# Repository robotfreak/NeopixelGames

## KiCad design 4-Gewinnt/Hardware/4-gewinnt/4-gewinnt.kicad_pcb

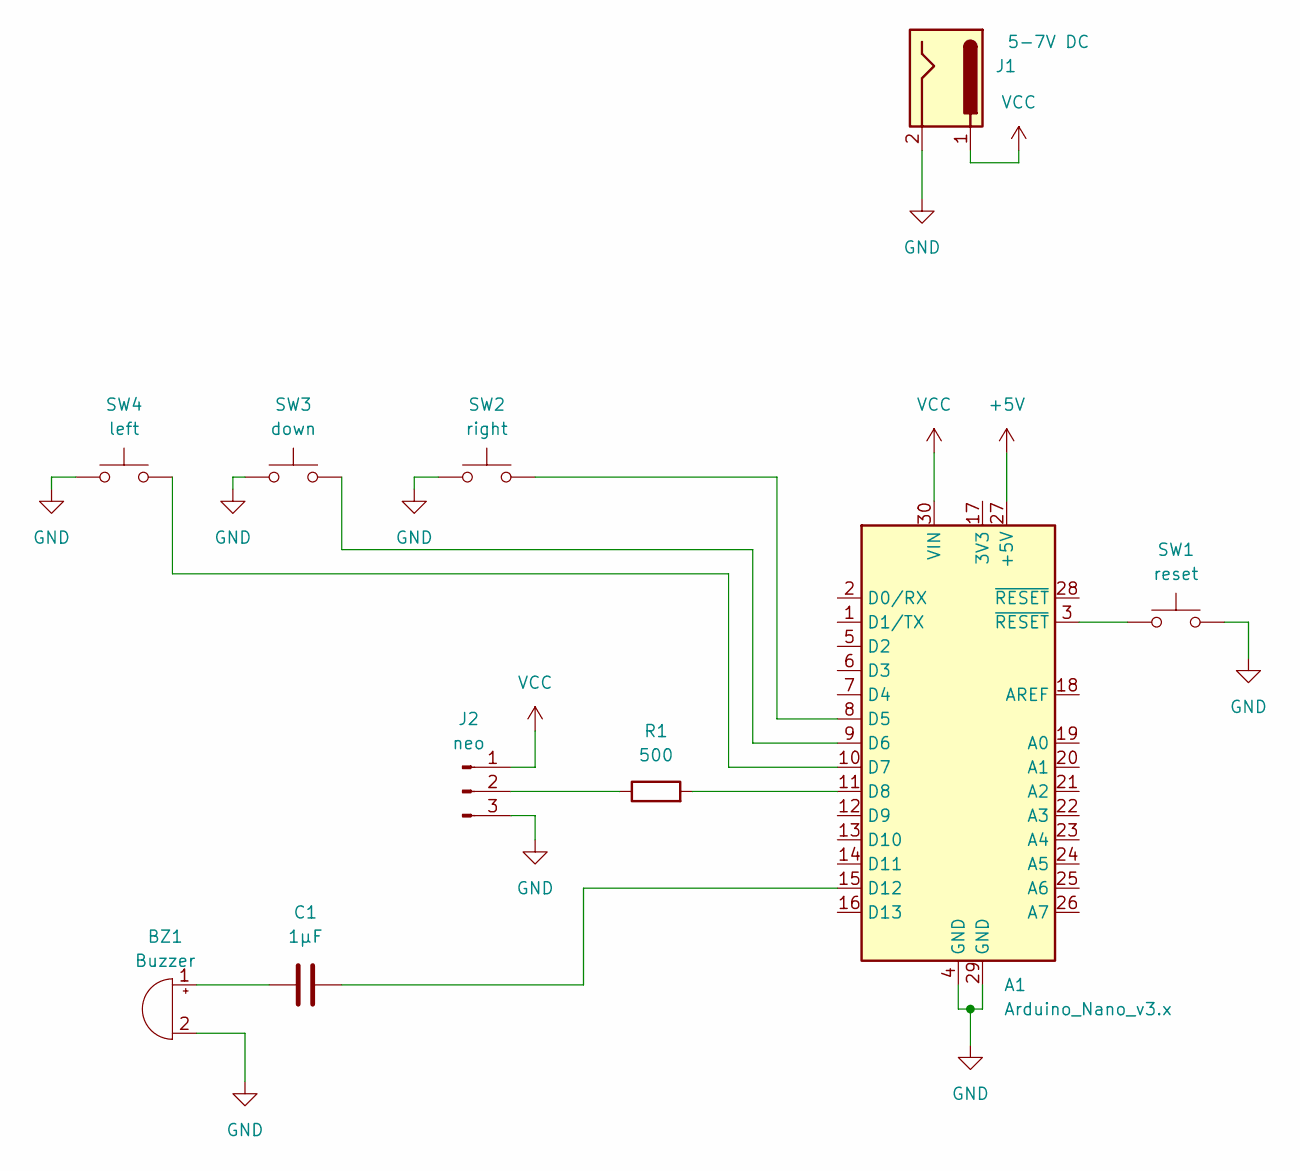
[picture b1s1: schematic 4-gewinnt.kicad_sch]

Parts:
A1: Arduino_Nano_v3.x; Arduino_Nano
BZ1: Buzzer; Buzzer_12x9.5RM7.6
C1: 1µF; C_Rect_L7.0mm_W2.0mm_P5.00mm
J1: 5-7V DC; PinHeader_1x02_P2.54mm_Vertical
J2: neo; PinHeader_1x03_P2.54mm_Vertical
R1: 500; R_Axial_DIN0207_L6.3mm_D2.5mm_P7.62mm_Horizontal
SW1: reset; PinHeader_1x02_P2.54mm_Vertical
SW2: right; PinHeader_1x02_P2.54mm_Vertical
SW3: down; PinHeader_1x02_P2.54mm_Vertical
SW4: left; PinHeader_1x02_P2.54mm_Vertical

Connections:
+5V: A1.27 (+5V)
GND: A1.4 (GND), A1.29 (GND), BZ1.2 (-), J1.2, J2.3, SW1.2, SW2.1, SW3.1, SW4.1
unnamed: A1.8 (D5), SW2.2
unnamed: A1.9 (D6), SW3.2
unnamed: A1.10 (D7), SW4.2
unnamed: A1.11 (D8), R1.2
unnamed: A1.15 (D12), C1.2
unnamed: A1.3 (~RESET), SW1.1
unnamed: BZ1.1 (+), C1.1
unnamed: J2.2, R1.1
VCC: A1.30 (VIN), J1.1, J2.1

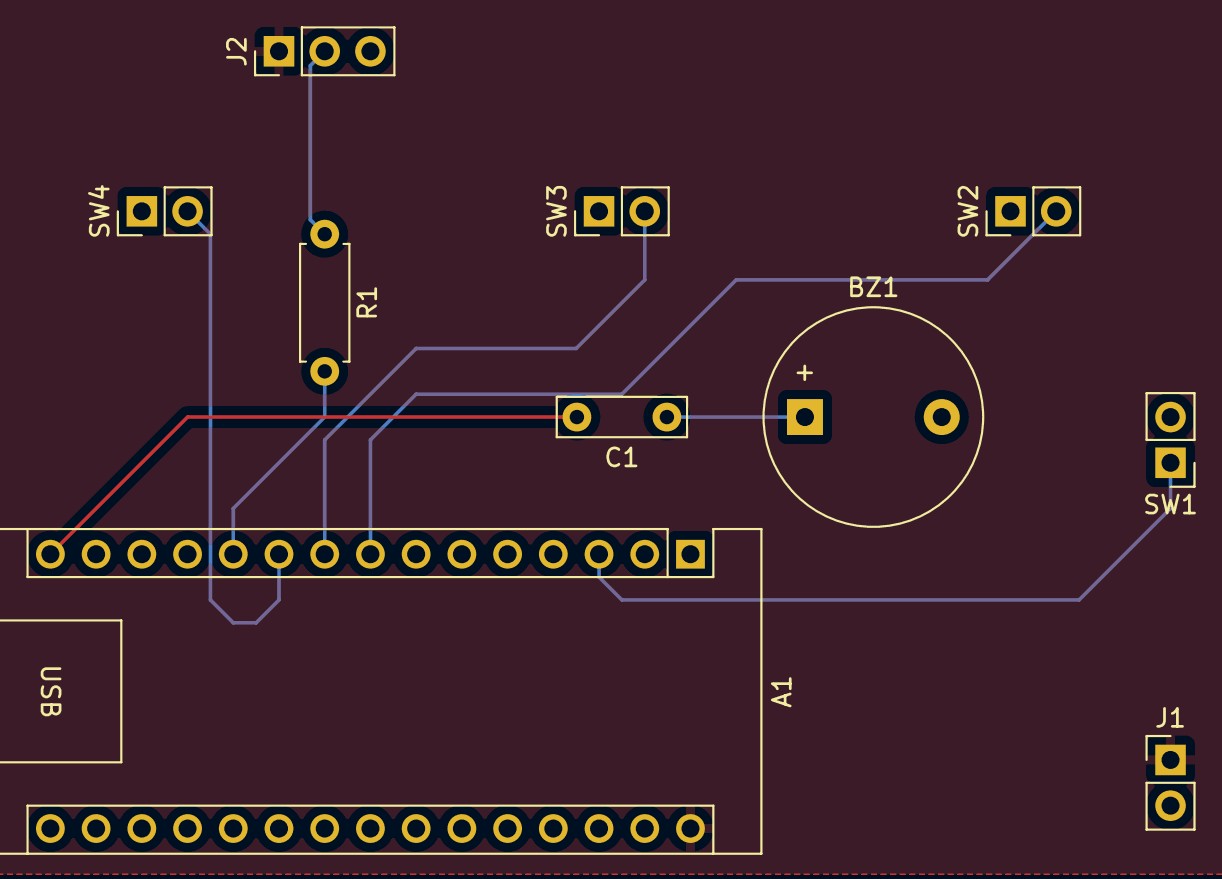
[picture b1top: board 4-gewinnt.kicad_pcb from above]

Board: 2 copper layers, 10 parts (0 on the bottom side), 10 nets.

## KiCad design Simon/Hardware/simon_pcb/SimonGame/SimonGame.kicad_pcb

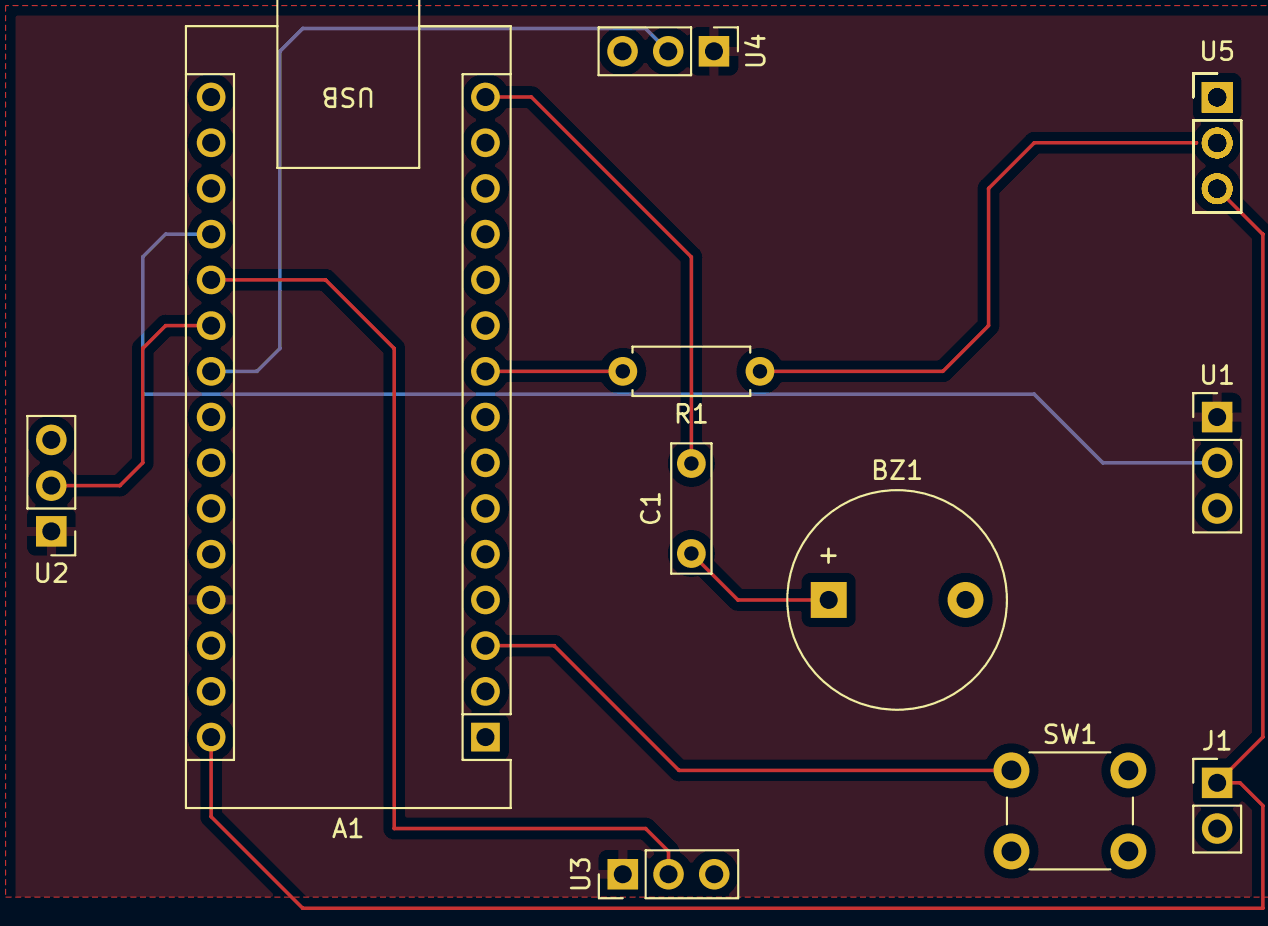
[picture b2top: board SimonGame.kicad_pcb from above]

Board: 2 copper layers, 14 parts (0 on the bottom side), 12 nets.

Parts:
A1: Arduino_Nano_v3.x; Arduino_Nano
BZ1: Buzzer; Buzzer_12x9.5RM7.6
C1: 1µF; C_Rect_L7.0mm_W2.0mm_P5.00mm
J1: 5-7V DC; PinHeader_1x02_P2.54mm_Vertical
R1: 500; R_Axial_DIN0207_L6.3mm_D2.5mm_P7.62mm_Horizontal
SW1: reset; SW_PUSH_6mm
U1, U5: blue; PinHeader_1x03_P2.54mm_Vertical
U2, U7: green; PinHeader_1x03_P2.54mm_Vertical
U3, U6: yellow; PinHeader_1x03_P2.54mm_Vertical
U4, U8: red; PinHeader_1x03_P2.54mm_Vertical

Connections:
+5V: A1.27 (+5V), U1.1 (VCC), U2.1 (VCC), U3.1 (VCC), U4.1 (VCC)
GND: A1.4 (GND), A1.29 (GND), BZ1.2 (-), J1.2, SW1.2, U1.3 (GND), U2.3 (GND), U3.3 (GND), U4.3 (GND), U5.1 (GND), U6.1 (GND), U7.1 (GND), U8.1 (GND)
unnamed: A1.19 (A0), U1.2 (O)
unnamed: A1.20 (A1), U3.2 (O)
unnamed: A1.21 (A2), U2.2 (O)
unnamed: A1.22 (A3), U4.2 (O)
unnamed: A1.9 (D6), R1.2
unnamed: A1.15 (D12), C1.2
unnamed: A1.3 (~RESET), SW1.1
unnamed: BZ1.1 (+), C1.1
unnamed: R1.1, U5.2 (DIN)
VCC: A1.30 (VIN), J1.1, U5.3 (VDC), U6.3 (VDC), U7.3 (VDC), U8.3 (VDC)

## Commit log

2024-06-25 remove not needed variables
2024-06-25 remove more unused variables
2024-06-26 added olr code, documenation
2024-06-26 added doc
2024-06-26 added simon schematic pcb
2024-06-26 added olr pcb, schematic pdf
2024-06-26 added simon pcb, schematic pdf
2024-06-27 added -gewinnt pcb schematics
2024-06-27 minor changes
